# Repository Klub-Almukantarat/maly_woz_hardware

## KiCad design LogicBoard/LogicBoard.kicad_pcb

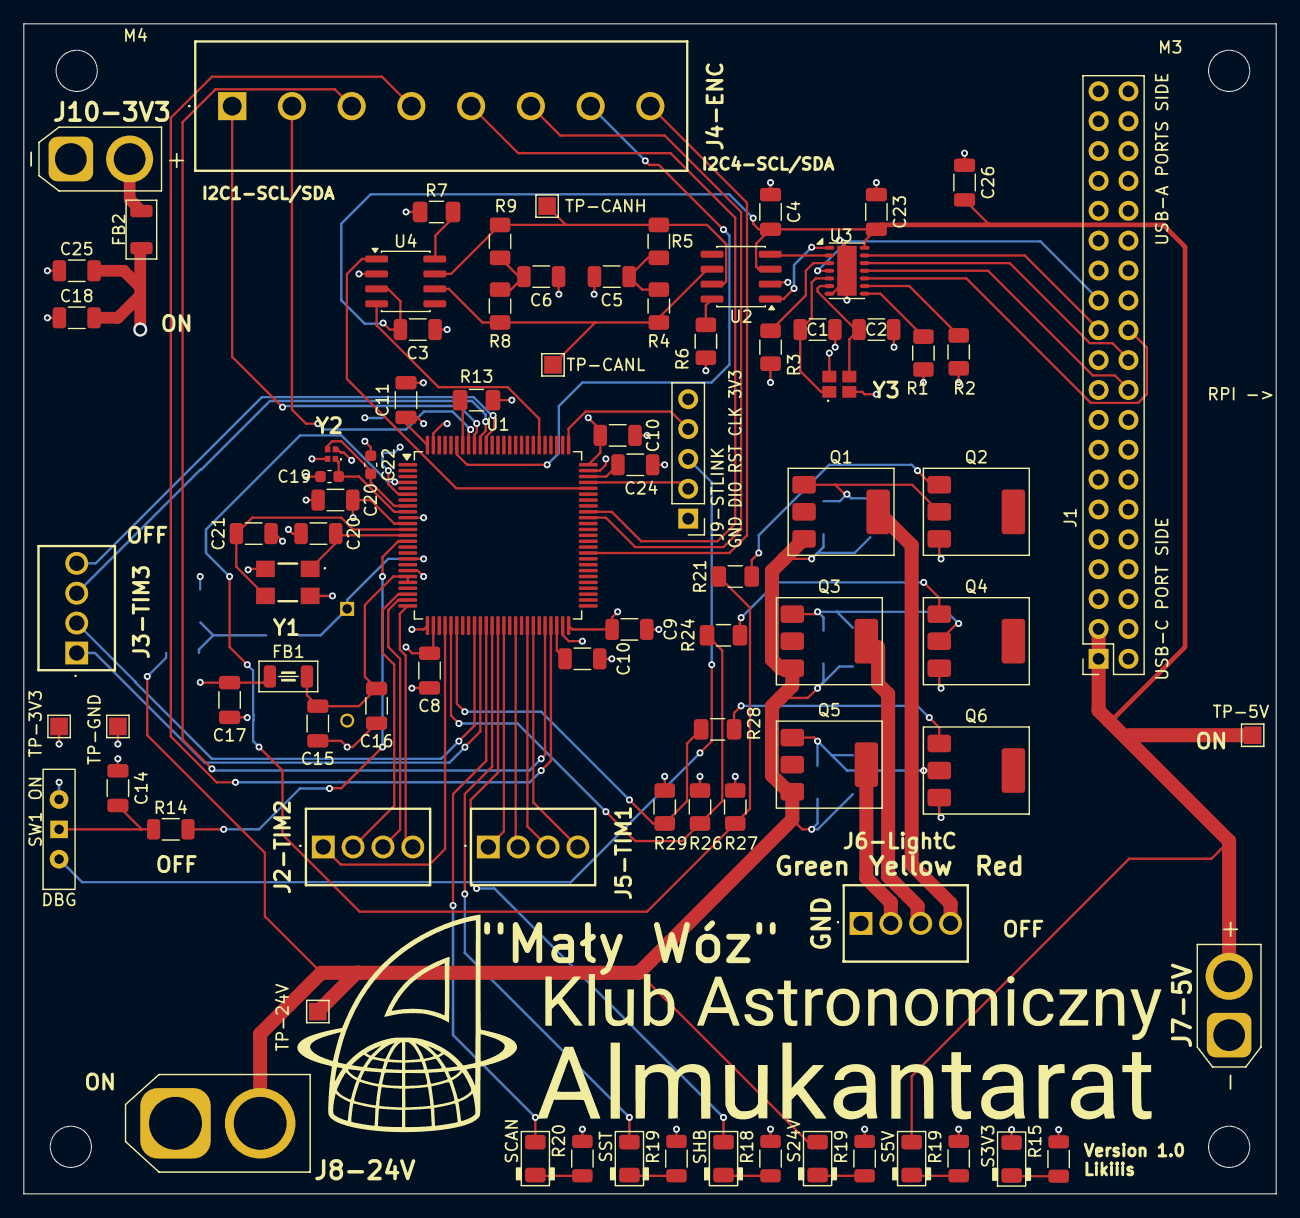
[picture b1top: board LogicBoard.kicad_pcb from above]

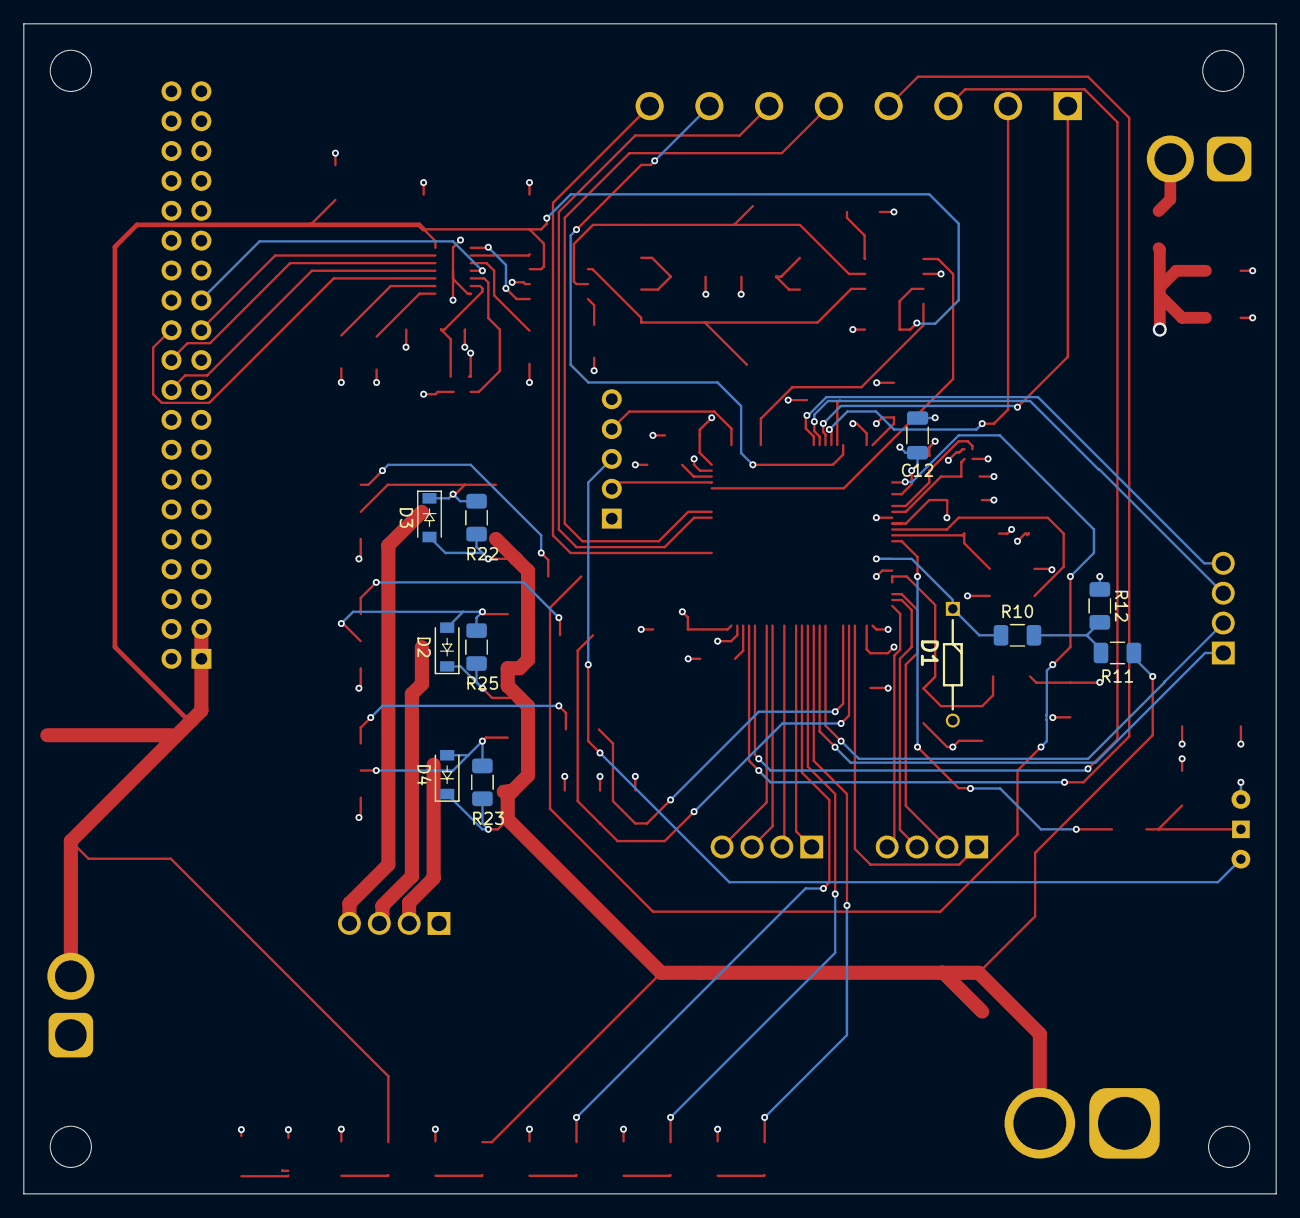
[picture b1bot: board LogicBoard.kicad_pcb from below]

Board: 4 copper layers, 106.5 x 99.5 mm, 101 parts (11 on the bottom side), 76 nets.

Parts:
C1, C2, C3, C4, C5, C6, C8, C9, C10, C10#2, C11, C12, C14, C15, C16, C17, C18, C20, C20#2, C21, C23, C24, C25, C26: C_1206_3216Metric
C19, C22: C_0603_1608Metric
D1: DIOAD950W60L350D150
D2, D4: ?; D_SOD-123
D3: D3; D_SOD-123
FB1, FB2: Ferrite_1206_3216Metric
J1: PinSocket_2x20_P2.54mm_Vertical
J2-TIM2, J3-TIM3, J5-TIM1, J6-LightC: TBC05041GG
J4-ENC: TBJ05081GG
J7-5V, J10-3V3: AMASS_XT30U-F_1x02_P5.0mm_Vertical
J8-24V: AMASS_XT60-F_1x02_P7.20mm_Vertical
J9-STLINK: PINHD_1x5_Male; PinHeader_1x05_P2.54mm_Vertical
M1, M2, M3, M4: MountingHole_3.5mm
Q1, Q2, Q3, Q4, Q5, Q6: SOT-223
R1, R2, R3, R4, R5, R6, R7, R8, R9, R10, R11, R12, R13, R14, R15, R18, R19, R19#2, R19#3, R20, R21, R22, R23, R24, R25, R26, R27, R28, R29: R_1206_3216Metric
S3V3, S5V, S24V: LED_1206; LED_1206_3216Metric
SCAN: LED_1206; LED_1206_3216Metric
SHB: LED_1206; LED_1206_3216Metric
SST: LED_1206; LED_1206_3216Metric
SW1: SW_Wuerth_450301014042; SW_Slide-03_Wuerth-WS-SLTV_10x2.5x6.4_P2.54mm
TP-3V3, TP-5V, TP-24V: TestPoint_Pad_1.5x1.5mm
TP-CANH: TestPoint_Pad_1.5x1.5mm
TP-CANL: TestPoint_Pad_1.5x1.5mm
TP-GND: TestPoint_Pad_1.5x1.5mm
U1: STM32H743VITx; LQFP-100_14x14mm_P0.5mm
U2, U4: MCP2557FD-xSN; SOIC-8_3.9x4.9mm_P1.27mm
U3: MCP2518FD-xQBB; DFN-14-1EP_3x4.5mm_P0.65mm_EP1.65x4.25mm
Y1: 7I25000F18UCG; 830033075
Y2: ABS04W32768KHZ6D2T5
Y3: Q24FA20H00209; ECS400936BCKYTR

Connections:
+3V3: C8.1, C9.1, C10.1, C11.2, C12.2, C17.1, C18.2, C20#2.1, C25.2, FB1.1, FB2.1, FB2.2, J9-STLINK.5, J10-3V3.2, S3V3.2 (A), SW1.3 (A), TP-3V3.1, U1.6 (VBAT), U1.11 (VDD), U1.27 (VDD), U1.50 (VDD), U1.75 (VDD), U1.100 (VDD)
+5V: C3.1, C4.1, C23.1, C26.1, J1.1, J1.3, J7-5V.2, S5V.2 (A), TP-5V.1, U2.3 (VDD), U3.14 (VDD), U4.3 (VDD)
+24V: D2.1, D3.2, D4.1, J8-24V.2, Q1.3, Q3.3, Q5.3, R11.2, R22.1, R23.1, R25.1, S24V.2 (A), TP-24V.1
BatteryHealth: D1.1, R10.1, R10.2, R11.1, R12.2, U1.17 (PC2_C)
CANActivity: SCAN.2 (A), U1.36 (PB2)
CanH: R5.2, R9.2, TP-CANH.1, U2.7 (CANH), U4.7 (CANH)
CanL: R4.1, R8.1, TP-CANL.1, U2.6 (CANL), U4.6 (CANL)
Cnn: C5.2, R4.2, R5.1
Cnn1: C6.1, R8.2, R9.1
DEBUG_RST: J9-STLINK.3, SW1.2 (C)
DEBUG_SWCLK: J9-STLINK.4, U1.76 (PA14)
DEBUG_SWDIO: J9-STLINK.2, U1.72 (PA13)
FDCAN_RX: U1.81 (PD0), U4.4 (RXD)
FDCAN_TX: U1.71 (PA12), U4.1 (TXD)
GND: C1.1, C2.2, C3.2, C4.2, C5.1, C6.2, C8.2, C9.2, C10.2, C10#2.2, C11.1, C12.1, C14.1, C15.2, C16.2, C17.2, C18.1, C19.2, C20.2, C20#2.2, C21.1, C22.1, C23.2, C24.2, C25.1, C26.2, D1.2, J1.5, J1.10, J1.13, J1.19, J1.26, J1.29, J1.33, J1.40, J6-LightC.1, J7-5V.1, J8-24V.1, J9-STLINK.1, J10-3V3.1, Q2.3, Q4.3, Q6.3, R1.1, R2.1, R3.1, R6.1, R7.1, R12.1, R13.1, R15.1, R18.1, R19.1, R19#2.1, R19#3.1, R20.1, R26.2, R27.2, R29.2, TP-GND.1, U1.10 (VSS), U1.19 (VSSA), U1.26 (VSS), U1.49 (VSS), U1.74 (VSS), U1.99 (VSS), U2.2 (VSS), U3.7 (VSS), U3.15 (VSS), U4.2 (VSS), Y1.2, Y1.4, Y2.2, Y2.4, Y3.2, Y3.4
GreenLight_Modulated: J6-LightC.2, Q5.4
HeartBeat: SHB.2 (A), U1.38 (PE8)
I2C1_SCL: J4-ENC.1, U1.92 (PB6)
I2C1_SDA: J4-ENC.2, U1.93 (PB7)
I2C2_SCL: J4-ENC.3, U1.46 (PB10)
I2C2_SDA: J4-ENC.4, U1.47 (PB11)
I2C3_SCL: J4-ENC.5, U1.67 (PA8)
I2C3_SDA: J4-ENC.6, U1.66 (PC9)
I2C4_SCL: J4-ENC.7, U1.95 (PB8)
I2C4_SDA: J4-ENC.8, U1.60 (PD13)
unnamed: C1.2, U3.5 (OSC2), Y3.1
unnamed: C2.1, U3.6 (OSC1), Y3.3
unnamed: C10#2.1, U1.48 (VCAP)
unnamed: C14.2, R14.1, SW1.1 (B)
unnamed: C19.1, U1.9 (PC15), Y2.1
unnamed: C20.1, U1.13 (PH1), Y1.1
unnamed: C21.2, U1.12 (PH0), Y1.3
unnamed: C22.2, U1.8 (PC14), Y2.3
unnamed: C24.1, U1.73 (VCAP)
unnamed: R15.2, S3V3.1 (K)
unnamed: R19.2, S5V.1 (K)
unnamed: R19#2.2, S24V.1 (K)
unnamed: R18.2, SHB.1 (K)
unnamed: R19#3.2, SST.1 (K)
unnamed: R20.2, SCAN.1 (K)
unnamed: R1.2, U3.8 (~INT1/GPIO1)
unnamed: R2.2, U3.9 (~INT0/GPIO0/XSTBY)
unnamed: R3.2, U3.3 (CLKO/SOF)
unnamed: R6.2, U2.8 (S)
unnamed: R7.2, U4.8 (S)
unnamed: R13.2, U1.94 (BOOT0)
unnamed: R14.2, U1.14 (NRST)
unnamed: U2.4 (RXD), U3.2 (RXCAN)
unnamed: U2.1 (TXD), U3.1 (TXCAN)
Q1-Q2: D3.1, Q1.1, Q2.2, R22.2
Q3-Q4: D2.2, Q3.1, Q4.2, R25.2
Q5-Q6: D4.2, Q5.1, Q6.2, R23.2
RedLight_Modulated: J6-LightC.4, Q1.4
SPI1_CS: J1.23, U3.13 (~CS)
SPI1_INT: J1.25, U3.4 (~INT)
SPI1_SCLK: J1.24, U3.10 (SCK)
SPI1_SDI: J1.20, U3.11 (SDI)
SPI1_SDO: J1.22, U3.12 (SDO)
StatusLED: SST.2 (A), U1.37 (PE7)
TIM1_CH1: J5-TIM1.1, U1.39 (PE9)
TIM1_CH2: J5-TIM1.2, U1.41 (PE11)
TIM1_CH3: J5-TIM1.3, U1.43 (PE13)
TIM1_CH4: J5-TIM1.4, U1.44 (PE14)
TIM2_CH1: J2-TIM2.1, U1.29 (PA5)
TIM2_CH2: J2-TIM2.2, U1.23 (PA1)
TIM2_CH3: J2-TIM2.3, U1.24 (PA2)
TIM2_CH4: J2-TIM2.4, U1.25 (PA3)
TIM3_CH1: J3-TIM3.4, U1.90 (PB4)
TIM3_CH2: J3-TIM3.3, U1.91 (PB5)
TIM3_CH3: J3-TIM3.2, U1.34 (PB0)
TIM3_CH4: J3-TIM3.1, U1.35 (PB1)
TIM13: Q4.1, R24.1, R24.2, R26.1, U1.30 (PA6)
TIM14: Q6.1, R28.1, R28.2, R29.1, U1.31 (PA7)
TIM15: Q2.1, R21.1, R21.2, R27.1, U1.4 (PE5)
VDDA_Conn: C15.1, C16.1, FB1.2, U1.20 (VREF+), U1.21 (VDDA)
YellowLight_Modulated: J6-LightC.3, Q3.4

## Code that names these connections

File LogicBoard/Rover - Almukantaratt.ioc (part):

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Mcu.Name=STM32H743VITx
Mcu.Package=LQFP100
Mcu.UserName=STM32H743VITx
PA1.Signal=S_TIM2_CH2
PA12.Mode=FDCAN_Activate
PA12.Signal=FDCAN1_TX
PA13\ (JTMS/SWDIO).Mode=Serial_Wire
PA13\ (JTMS/SWDIO).Signal=DEBUG_JTMS-SWDIO
PA14\ (JTCK/SWCLK).Mode=Serial_Wire
PA14\ (JTCK/SWCLK).Signal=DEBUG_JTCK-SWCLK
PA2.Signal=S_TIM2_CH3
PA3.Signal=S_TIM2_CH4
PA5.Signal=S_TIM2_CH1_ETR
PA6.Signal=S_TIM13_CH1
PA7.Signal=S_TIM14_CH1
PA8.Mode=I2C
PA8.Signal=I2C3_SCL
PB0.Signal=S_TIM3_CH3
PB1.Signal=S_TIM3_CH4
PB10.Mode=I2C
PB10.Signal=I2C2_SCL
PB11.Mode=I2C
PB11.Signal=I2C2_SDA
PB4\ (NJTRST).Signal=S_TIM3_CH1
PB5.Signal=S_TIM3_CH2
PB6.Mode=I2C
PB6.Signal=I2C1_SCL
PB7.Mode=I2C
PB7.Signal=I2C1_SDA
PB8.Mode=I2C
PB8.Signal=I2C4_SCL
PC14-OSC32_IN\ (OSC32_IN).Mode=LSE-External-Oscillator
PC14-OSC32_IN\ (OSC32_IN).Signal=RCC_OSC32_IN
PC15-OSC32_OUT\ (OSC32_OUT).Mode=LSE-External-Oscillator
PC15-OSC32_OUT\ (OSC32_OUT).Signal=RCC_OSC32_OUT
PC2_C.Mode=IN0-Single-Ended
PC2_C.Signal=ADC3_INP0
PC9.Mode=I2C
PC9.Signal=I2C3_SDA
PD0.Mode=FDCAN_Activate
PD0.Signal=FDCAN1_RX
PD13.Mode=I2C
PD13.Signal=I2C4_SDA
PE11.Signal=S_TIM1_CH2
PE13.Signal=S_TIM1_CH3
PE14.Signal=S_TIM1_CH4
PE5.Signal=S_TIM15_CH1
PE9.Signal=S_TIM1_CH1
PH0-OSC_IN\ (PH0).Mode=HSE-External-Oscillator
PH0-OSC_IN\ (PH0).Signal=RCC_OSC_IN
PH1-OSC_OUT\ (PH1).Mode=HSE-External-Oscillator
PH1-OSC_OUT\ (PH1).Signal=RCC_OSC_OUT
RCC.SYSCLKFreq_VALUE=64000000
board=custom
